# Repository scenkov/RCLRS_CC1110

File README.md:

RC LRS Tx/Rx - 8ch with TI CC1110 32kb.

for this project I'm using 'CC1110+PA+LNA-470MHz' wireless module - Output power 18-23dbm, 
and get more that 12km of ground range.

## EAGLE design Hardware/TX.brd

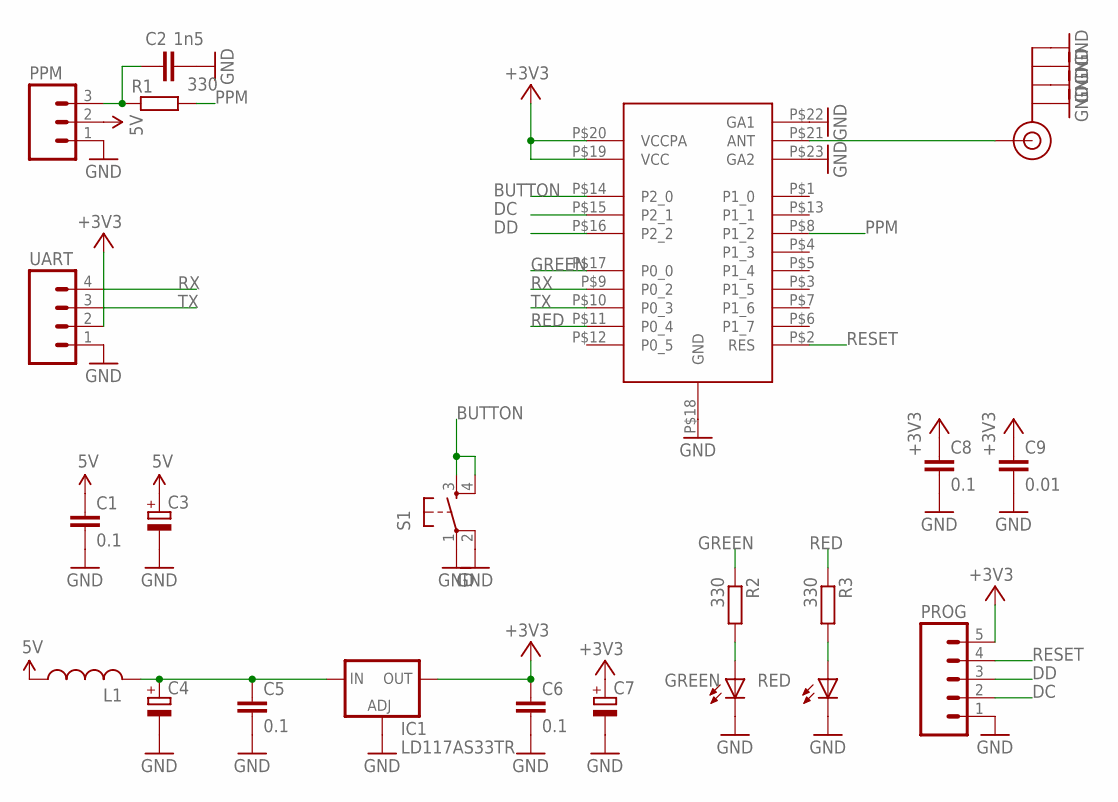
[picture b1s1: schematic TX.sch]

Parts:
C1, C5, C6, C8: 0.1; C0603
C2: 1n5; C0603
C3, C4, C7: CPOL-EUCT3216; CT3216
C9: 0.01; C0603
GREEN: LEDCHIPLED_1206; CHIPLED_1206
IC1: LD117AS33TR; SOT223
J$1: SMA_EDGE; SMA-EDGE
L1: L-USL2012C; L2012C
PPM: M03PTH; 1X03
PROG: M05PTH; 1X05
R1, R2, R3: 330; MINI_MELF-0102R
RED: LEDCHIPLED_1206; CHIPLED_1206
S1: TAC_SWITCHSMD; TACTILE_SWITCH_SMD
U$1: CC1110_PA
UART: M04PTH; 1X04

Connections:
5V: C1.1, C3.+, L1.1, PPM.2
+3V3: C6.1, C7.+, C8.1, C9.1, IC1.4 (OUT), PROG.5, U$1.P$19 (VCC), U$1.P$20 (VCCPA), UART.2
BUTTON: S1.3, S1.4, U$1.P$14 (P2_0)
DC: PROG.2, U$1.P$15 (P2_1)
DD: PROG.3, U$1.P$16 (P2_2)
GND: C1.2, C2.2, C3.-, C4.-, C5.2, C6.2, C7.-, C8.2, C9.2, GREEN.C, IC1.1 (ADJ), J$1.GND@0 (GND), J$1.GND@1 (GND), J$1.GND@2 (GND), J$1.GND@3 (GND), PPM.1, PROG.1, RED.C, S1.1, S1.2, U$1.P$18 (GND), U$1.P$22 (GA1), U$1.P$23 (GA2), UART.1
GREEN: R2.1, U$1.P$17 (P0_0)
unnamed: J$1.SIG (SIGNAL), U$1.P$21 (ANT)
unnamed: C4.+, C5.1, IC1.3 (IN), L1.2
unnamed: GREEN.A, R2.2
unnamed: R3.2, RED.A
unnamed: C2.1, PPM.3, R1.1
PPM: R1.2, U$1.P$8 (P1_2)
RED: R3.1, U$1.P$11 (P0_4)
RESET: PROG.4, U$1.P$2 (RES)
RX: U$1.P$9 (P0_2), UART.4
TX: U$1.P$10 (P0_3), UART.3

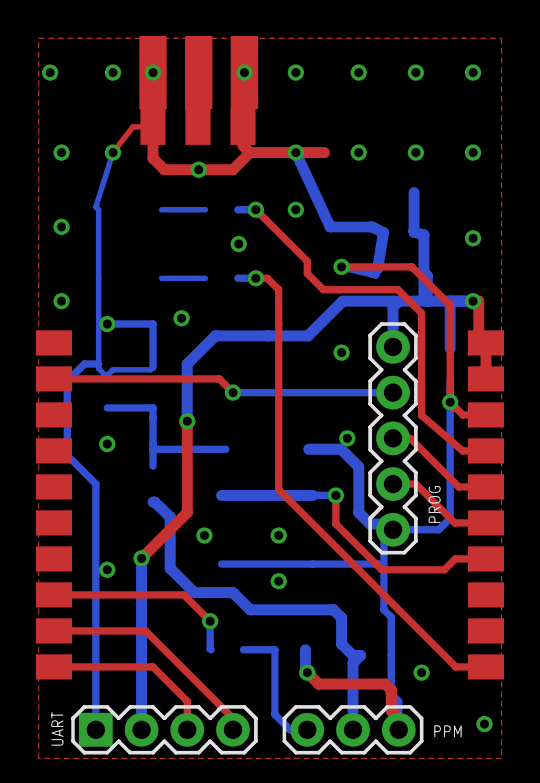
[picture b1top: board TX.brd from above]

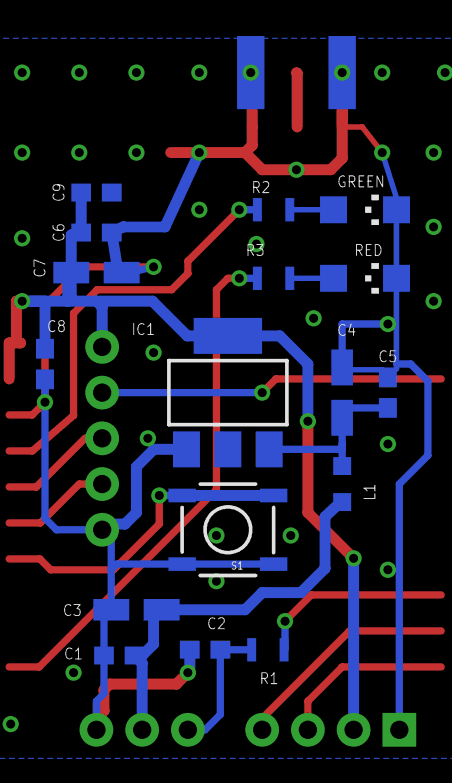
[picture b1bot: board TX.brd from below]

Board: 2 copper layers, 22 parts (17 on the bottom side), 17 nets.

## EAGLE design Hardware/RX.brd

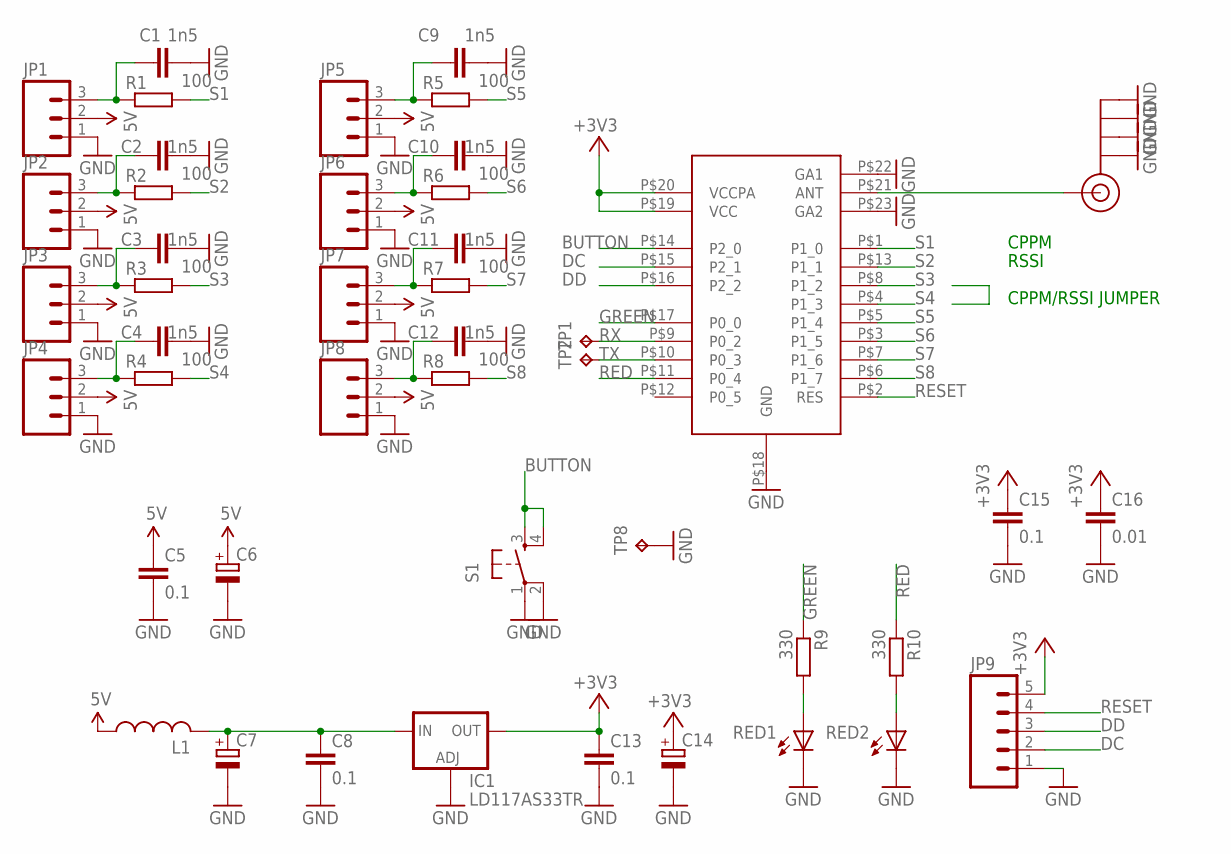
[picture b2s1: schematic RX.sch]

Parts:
C1, C2, C3, C4, C9, C10, C11, C12: 1n5; C0603
C5, C8, C13, C15: 0.1; C0603
C6, C7, C14: CPOL-EUCT3216; CT3216
C16: 0.01; C0603
IC1: LD117AS33TR; SOT223
J$1: SMA_EDGE; SMA-EDGE
JP1, JP2, JP3, JP4, JP5, JP6, JP7, JP8: M03PTH; 1X03
JP9: M05PTH; 1X05
L1: L-USL2012C; L2012C
R1, R2, R3, R4, R5, R6, R7, R8: 100; MINI_MELF-0102R
R9, R10: 330; MINI_MELF-0102R
RED1, RED2: LEDCHIPLED_1206; CHIPLED_1206
S1: TAC_SWITCHSMD; TACTILE_SWITCH_SMD
TP1, TP2, TP8: TPB1,27; B1,27
U$1: CC1110_PA

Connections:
5V: C5.1, C6.+, JP1.2, JP2.2, JP3.2, JP4.2, JP5.2, JP6.2, JP7.2, JP8.2, L1.1
+3V3: C13.1, C14.+, C15.1, C16.1, IC1.4 (OUT), JP9.5, U$1.P$19 (VCC), U$1.P$20 (VCCPA)
BUTTON: S1.3, S1.4, U$1.P$14 (P2_0)
DC: JP9.2, U$1.P$15 (P2_1)
DD: JP9.3, U$1.P$16 (P2_2)
GND: C1.2, C2.2, C3.2, C4.2, C5.2, C6.-, C7.-, C8.2, C9.2, C10.2, C11.2, C12.2, C13.2, C14.-, C15.2, C16.2, IC1.1 (ADJ), J$1.GND@0 (GND), J$1.GND@1 (GND), J$1.GND@2 (GND), J$1.GND@3 (GND), JP1.1, JP2.1, JP3.1, JP4.1, JP5.1, JP6.1, JP7.1, JP8.1, JP9.1, RED1.C, RED2.C, S1.1, S1.2, TP8.TP, U$1.P$18 (GND), U$1.P$22 (GA1), U$1.P$23 (GA2)
GREEN: R9.1, U$1.P$17 (P0_0)
unnamed: J$1.SIG (SIGNAL), U$1.P$21 (ANT)
unnamed: C7.+, C8.1, IC1.3 (IN), L1.2
unnamed: R9.2, RED1.A
unnamed: R10.2, RED2.A
unnamed: C9.1, JP5.3, R5.1
unnamed: C10.1, JP6.3, R6.1
unnamed: C11.1, JP7.3, R7.1
unnamed: C12.1, JP8.3, R8.1
unnamed: C1.1, JP1.3, R1.1
unnamed: C2.1, JP2.3, R2.1
unnamed: C3.1, JP3.3, R3.1
unnamed: C4.1, JP4.3, R4.1
RED: R10.1, U$1.P$11 (P0_4)
RESET: JP9.4, U$1.P$2 (RES)
RX: TP1.TP, U$1.P$9 (P0_2)
S1: R1.2, U$1.P$1 (P1_0)
S2: R2.2, U$1.P$13 (P1_1)
S3: R3.2, U$1.P$8 (P1_2)
S4: R4.2, U$1.P$4 (P1_3)
S5: R5.2, U$1.P$5 (P1_4)
S6: R6.2, U$1.P$3 (P1_5)
S7: R7.2, U$1.P$7 (P1_6)
S8: R8.2, U$1.P$6 (P1_7)
TX: TP2.TP, U$1.P$10 (P0_3)

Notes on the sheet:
CPPM
RSSI
CPPM/RSSI JUMPER

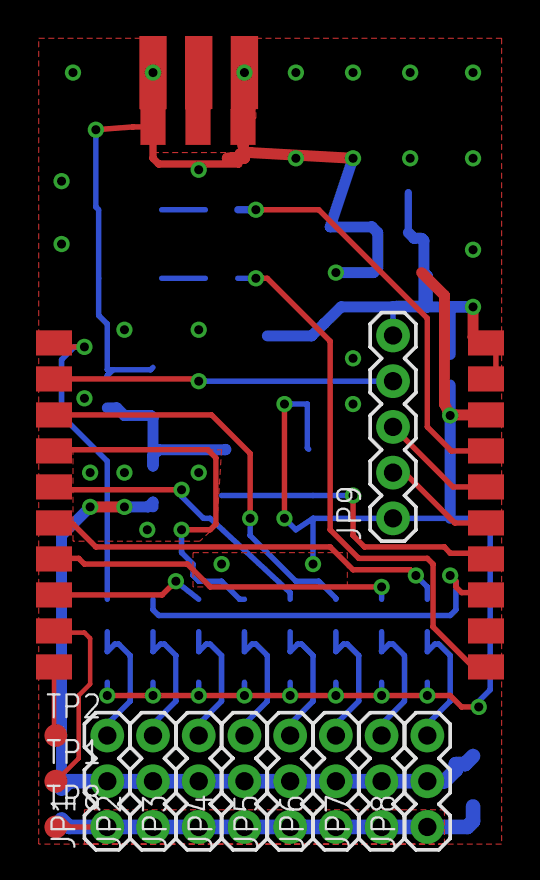
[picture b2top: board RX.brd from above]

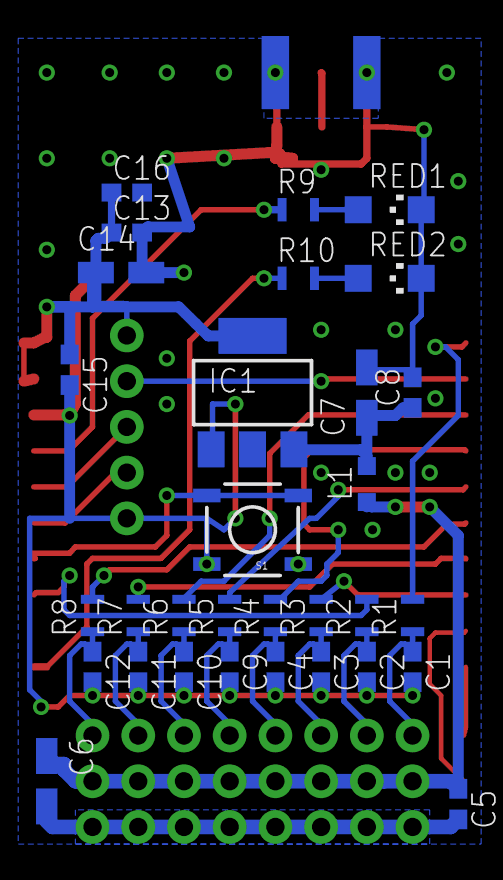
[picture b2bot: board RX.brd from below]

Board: 2 copper layers, 45 parts (31 on the bottom side), 31 nets.

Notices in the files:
parts and their libraries:
SparkFun-Connectors: Licensing: Creative Commons ShareAlike 4.0 International - https://creativecommons.org/licenses/by-sa/4.0
